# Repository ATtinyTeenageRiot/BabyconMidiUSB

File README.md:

## BabyconMidiUSB

## Installation

## Contributors

## Credits

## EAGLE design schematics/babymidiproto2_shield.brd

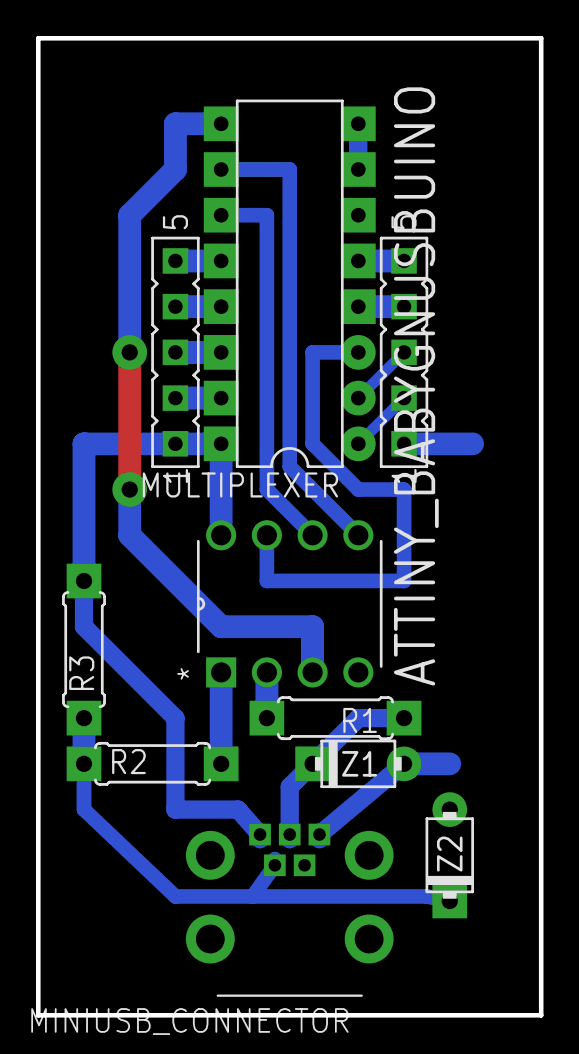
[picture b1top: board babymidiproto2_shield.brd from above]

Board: 2 copper layers, 27.9 x 54.3 mm, 10 parts (0 on the bottom side), 18 nets.

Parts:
ATTINY_BABYGNUSBUINO: TINY85-20-DIP; DIP254P762X533-8
MINIUSB_CONNECTOR: 6510051365212; MINIUSB_DIP
MULTIPLEXER: 4051N; DIL16
PINHEADER_1_4, PINHEADER_5_8: FE05-1-SQUARE-BIG
R1, R2: 68; 0703
R3: 1K5; 0703
Z1, Z2: 3.3V; DO41-2

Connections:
D_MINUS: ATTINY_BABYGNUSBUINO.1, R2.2
D_PLUS: ATTINY_BABYGNUSBUINO.2, R1.2
GND: ATTINY_BABYGNUSBUINO.4, MINIUSB_CONNECTOR.5, MULTIPLEXER.6, MULTIPLEXER.7, MULTIPLEXER.8, PINHEADER_5_8.1, Z1.A, Z2.A
INPUT_1: MULTIPLEXER.12, PINHEADER_1_4.5
INPUT_2: MULTIPLEXER.13, PINHEADER_1_4.4
INPUT_3: MULTIPLEXER.14, PINHEADER_1_4.3
INPUT_4: MULTIPLEXER.15, PINHEADER_1_4.2
INPUT_5: MULTIPLEXER.5, PINHEADER_5_8.5
INPUT_6: MULTIPLEXER.4, PINHEADER_5_8.4
INPUT_7: MULTIPLEXER.2, PINHEADER_5_8.3
INPUT_8: MULTIPLEXER.1, PINHEADER_5_8.2
MULTIPLEXED_ANALOG_PIN: ATTINY_BABYGNUSBUINO.7, MULTIPLEXER.3
unnamed: MINIUSB_CONNECTOR.3, R1.1, Z1.C
unnamed: MINIUSB_CONNECTOR.2, R2.1, R3.1, Z2.C
S1: ATTINY_BABYGNUSBUINO.6, MULTIPLEXER.11
S2: ATTINY_BABYGNUSBUINO.5, MULTIPLEXER.10
S3: ATTINY_BABYGNUSBUINO.3, MULTIPLEXER.9
VCC: ATTINY_BABYGNUSBUINO.8, MINIUSB_CONNECTOR.1, MULTIPLEXER.16, PINHEADER_1_4.1, R3.2

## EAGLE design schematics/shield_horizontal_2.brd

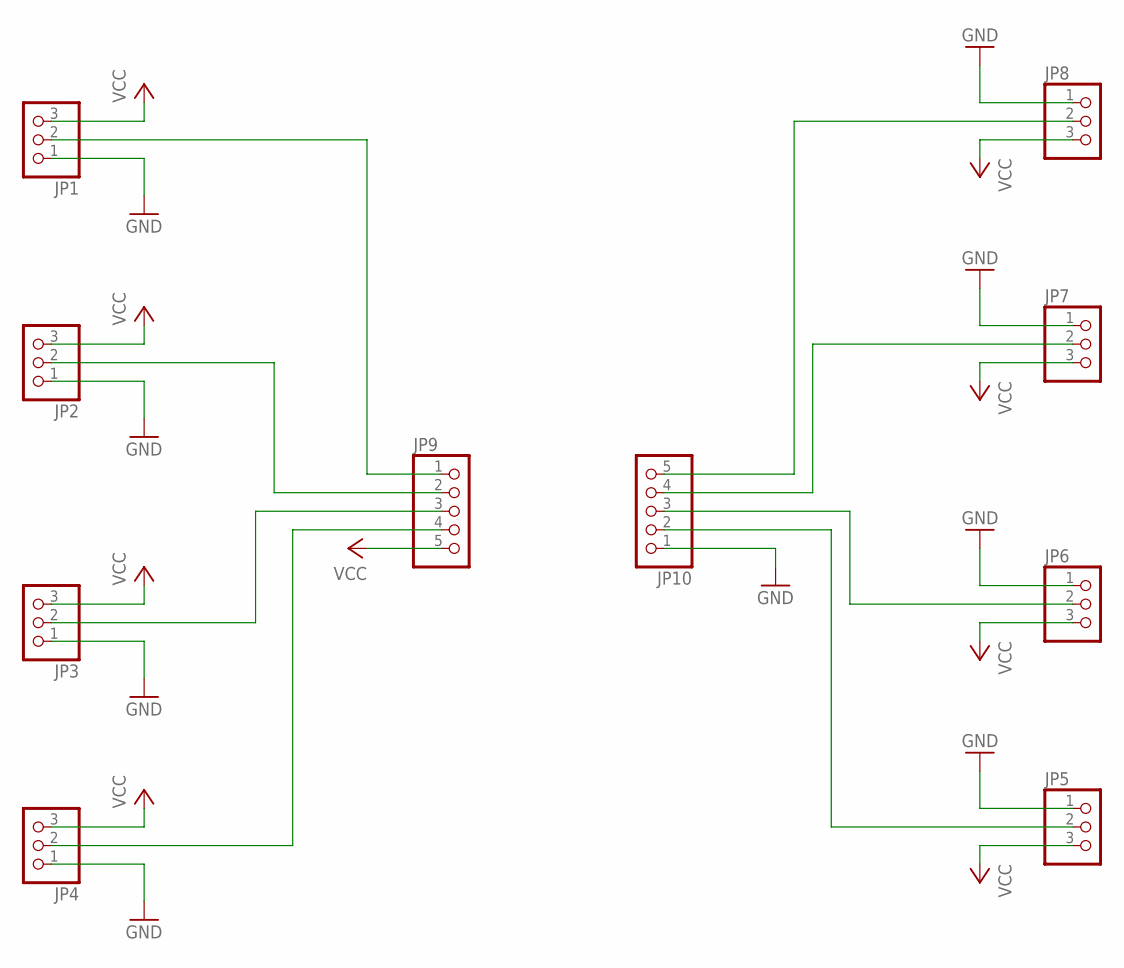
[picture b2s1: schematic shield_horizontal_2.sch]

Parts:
JP1, JP2, JP3, JP4, JP5, JP6, JP7, JP8: PINHD-1X3PS; 1X03-POTENTIOSHIELD
JP9, JP10: PINHD-1X5; 1X05

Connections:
GND: JP1.1, JP2.1, JP3.1, JP4.1, JP5.1, JP6.1, JP7.1, JP8.1, JP10.1
unnamed: JP1.2, JP9.1
unnamed: JP2.2, JP9.2
unnamed: JP3.2, JP9.3
unnamed: JP4.2, JP9.4
unnamed: JP5.2, JP10.2
unnamed: JP6.2, JP10.3
unnamed: JP7.2, JP10.4
unnamed: JP8.2, JP10.5
VCC: JP1.3, JP2.3, JP3.3, JP4.3, JP5.3, JP6.3, JP7.3, JP8.3, JP9.5

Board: 2 copper layers, 10 parts (0 on the bottom side), 10 nets, no tracks yet.

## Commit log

2015-10-28 fix symlinks
2015-11-03 reorder pin number
2015-11-29 shields
2015-11-29 horiz shield update
2015-11-29 board variant
2015-12-01 added analog pin noise removal
2015-12-01 added comment
2015-12-01 added puredata examples
2015-12-04 add shield horizontal type b
2015-12-06 Created babymidipin.png
2015-12-06 Updated babymidipin.png
2015-12-06 Created README.md
2015-12-16 updated to decoupled midi library
2015-12-21 fix usb disappear (because using direct delay fun)
2015-12-30 refactor schematic
2015-12-31 add midi config file
2015-12-31 add comment to enable android support
2016-03-07 update to teenymidi
